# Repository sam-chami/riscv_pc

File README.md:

# riscv_pc

A carrier board for the Lichee RV RISC-V SOM (System On Module).

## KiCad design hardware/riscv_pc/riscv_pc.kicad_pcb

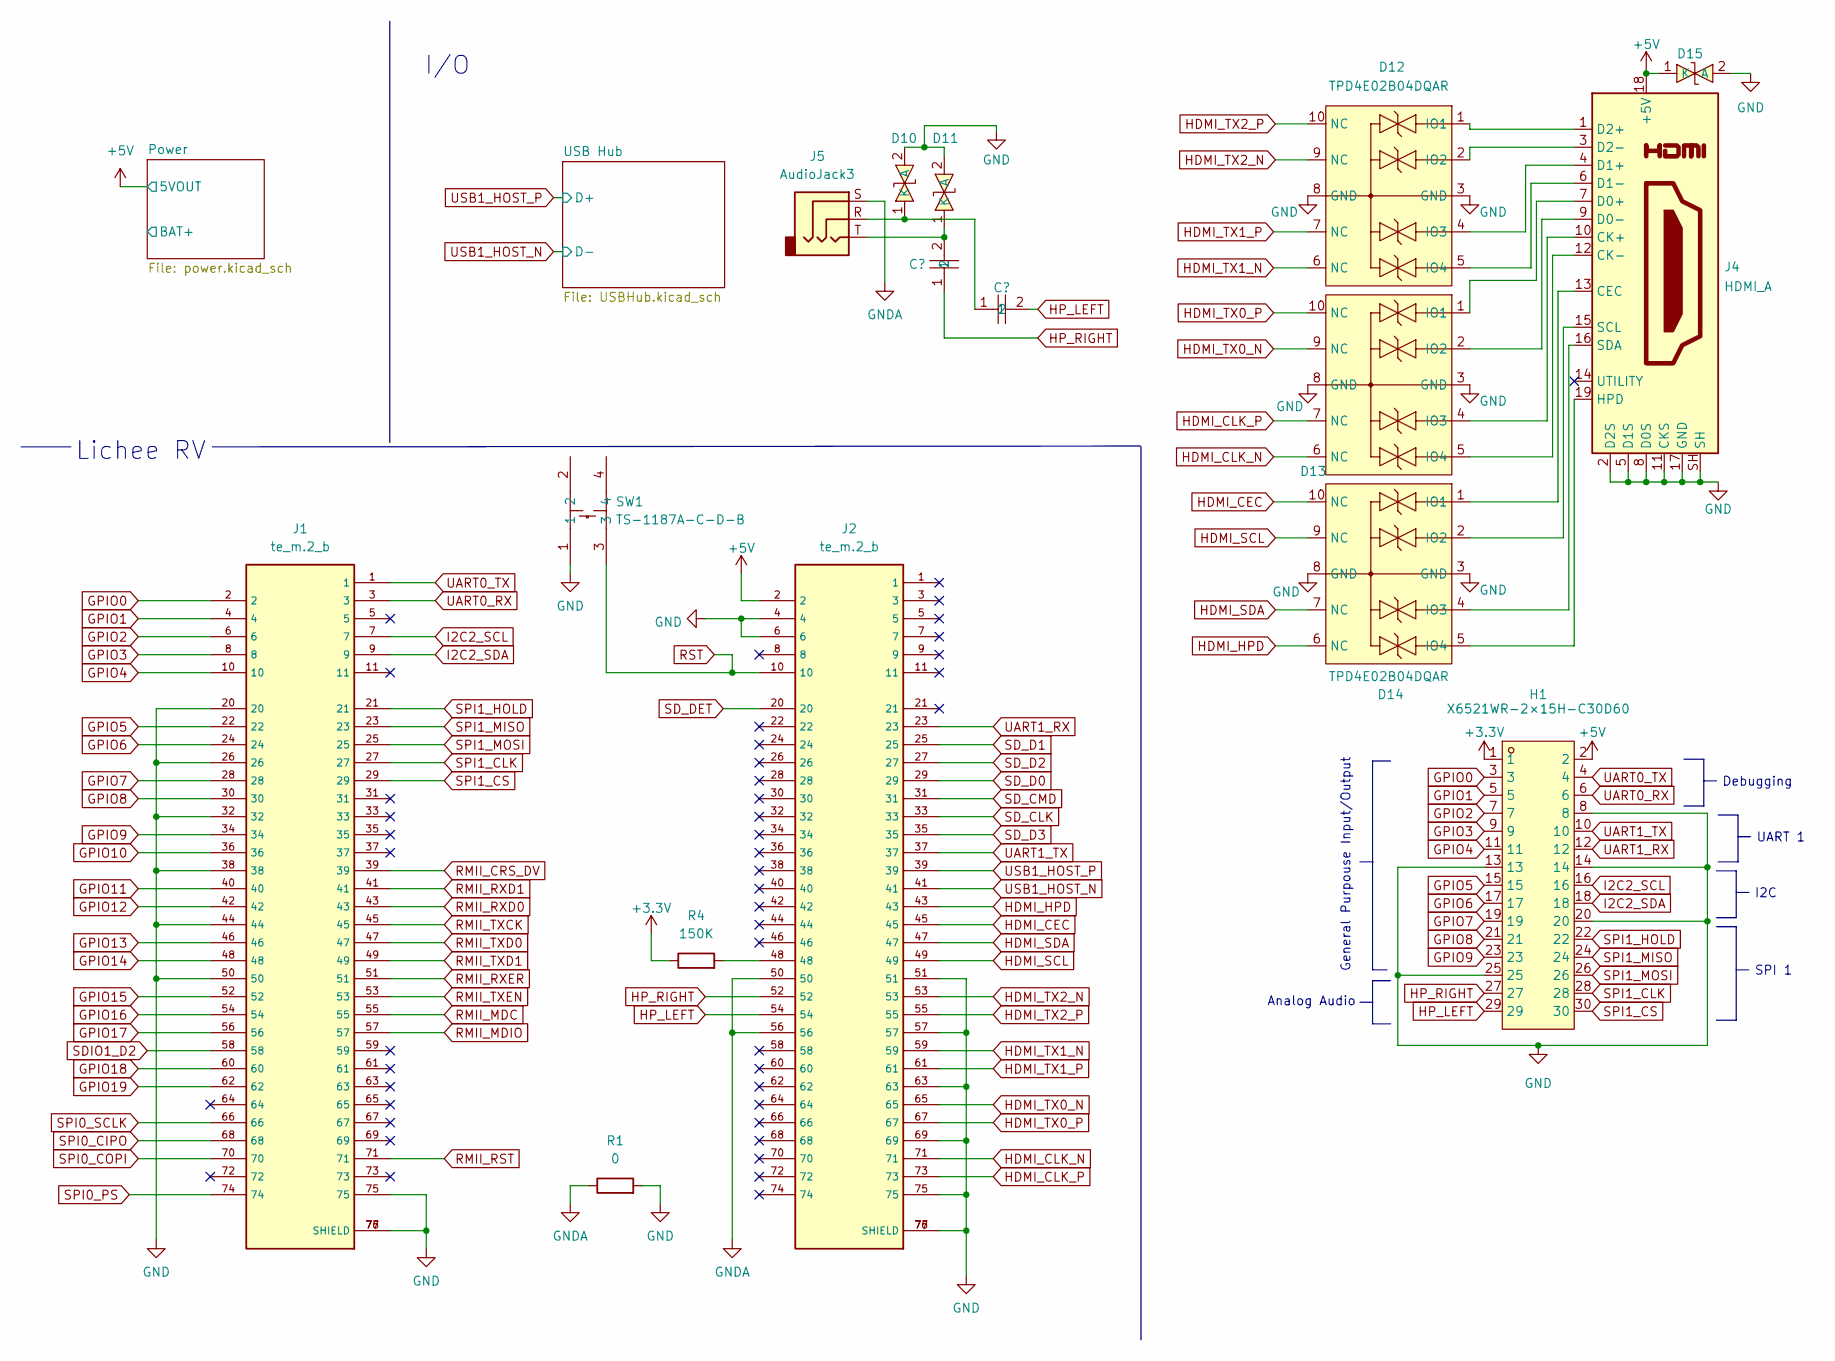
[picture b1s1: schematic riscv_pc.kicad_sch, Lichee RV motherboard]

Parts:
D10, D11, D15: GBLC08C-LF-T7; SOD-323_L1.8-W1.3-LS2.5-BI; LCSC Part C282422
D12, D13, D14: TPD4E02B04DQAR; USON-10_L2.5-W1.0-P0.50-BL; LCSC Part C106794
H1: X6521WR-2×15H-C30D60; HDR-TH_30P-P2.54-H-M-R2-C15-S2.54; LCSC Part C725927
J1, J2: te_m.2_b; CONN-SMD_AS0BC21-S30BB-7H; JLC C2761526
J4: HDMI_A; HDMI-SMD_HDMI-001S; JLC C720616
J5: AudioJack3; AUDIO-TH_PJ313D; JLC C18167
R1: 0; R_0603_1608Metric
R4: 150K; R_0603_1608Metric; JLC C22807
SW1: TS-1187A-C-D-B; KEY-SMD_4P-L5.2-W5.2-P3.7-LS6.4-TL; LCSC Part C318888

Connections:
+5V: D15.1 (K), H1.2, J2.2, J4.18 (+5V); also elsewhere on the board
GND: D10.2 (A), D11.2 (A), D12.3 (GND), D12.8 (GND), D13.3 (GND), D13.8 (GND), D14.3 (GND), D14.8 (GND), D15.2 (A), H1.8, H1.13, H1.14, H1.20, H1.25, J1.20, J1.26, J1.32, J1.38, J1.44, J1.50, J1.75, J1.76 (SHIELD), J1.77 (SHIELD), J2.4, J2.6, J2.51, J2.57, J2.63, J2.69, J2.75, J2.76 (SHIELD), J2.77 (SHIELD), J4.2 (D2S), J4.5 (D1S), J4.8 (D0S), J4.11 (CKS), J4.17 (GND), J4.SH, R1.2, SW1.1; also elsewhere on the board
GNDA: J2.50, J2.56, J5.S, R1.1
GPIO0: H1.3, J1.2
GPIO1: H1.5, J1.4
GPIO2: H1.7, J1.6
GPIO3: H1.9, J1.8
GPIO4: H1.11, J1.10
GPIO5: H1.15, J1.22
GPIO6: H1.17, J1.24
GPIO7: H1.19, J1.28
GPIO8: H1.21, J1.30
GPIO9: H1.23, J1.34
GPIO10: J1.36
GPIO11: J1.40
GPIO12: J1.42
GPIO13: J1.46
GPIO14: J1.48
GPIO15: J1.52
GPIO16: J1.54
GPIO17: J1.56
GPIO18: J1.60
GPIO19: J1.62
HDMI_CEC: D14.10 (NC), J2.45
HDMI_CLK_N: D13.6 (NC), J2.71
HDMI_CLK_P: D13.7 (NC), J2.73
HDMI_HPD: D14.6 (NC), J2.43
HDMI_SCL: D14.9 (NC), J2.49
HDMI_SDA: D14.7 (NC), J2.47
HDMI_TX0_N: D13.9 (NC), J2.65
HDMI_TX0_P: D13.10 (NC), J2.67
HDMI_TX1_N: D12.6 (NC), J2.59
HDMI_TX1_P: D12.7 (NC), J2.61
HDMI_TX2_N: D12.9 (NC), J2.53
HDMI_TX2_P: D12.10 (NC), J2.55
HP_LEFT: H1.29, J2.54; also elsewhere on the board
HP_RIGHT: H1.27, J2.52; also elsewhere on the board
I2C2_SCL: H1.16, J1.7
I2C2_SDA: H1.18, J1.9
unnamed 50: D10.1 (K), J5.R; also elsewhere on the board
unnamed 51: D11.1 (K), J5.T; also elsewhere on the board
unnamed: D12.1 (IO1), J4.1 (D2+)
unnamed: D12.2 (IO2), J4.3 (D2-)
unnamed: D12.4 (IO3), J4.4 (D1+)
unnamed: D12.5 (IO4), J4.6 (D1-)
unnamed: D13.1 (IO1), J4.7 (D0+)
unnamed: D13.2 (IO2), J4.9 (D0-)
unnamed: D13.4 (IO3), J4.10 (CK+)
unnamed: D13.5 (IO4), J4.12 (CK-)
unnamed: D14.1 (IO1), J4.13 (CEC)
unnamed: D14.2 (IO2), J4.15 (SCL)
unnamed: D14.4 (IO3), J4.16 (SDA)
unnamed: D14.5 (IO4), J4.19 (HPD)
unnamed: J2.48, R4.2
RMII_CRS_DV: J1.39
RMII_MDC: J1.55
RMII_MDIO: J1.57
RMII_RST: J1.71
RMII_RXD0: J1.43
RMII_RXD1: J1.41
RMII_RXER: J1.51
RMII_TXCK: J1.45
RMII_TXD0: J1.47
RMII_TXD1: J1.49
RMII_TXEN: J1.53
RST: J2.10, SW1.3
SDIO1_D2: J1.58
SD_CLK: J2.33
SD_CMD: J2.31
SD_D0: J2.29
SD_D1: J2.25
SD_D2: J2.27
SD_D3: J2.35
SD_DET: J2.20
SPI0_CIPO: J1.68
SPI0_COPI: J1.70
SPI0_PS: J1.74
SPI0_SCLK: J1.66
SPI1_CLK: H1.28, J1.27
SPI1_CS: H1.30, J1.29
SPI1_HOLD: H1.22, J1.21
SPI1_MISO: H1.24, J1.23
SPI1_MOSI: H1.26, J1.25
UART0_RX: H1.6, J1.3
UART0_TX: H1.4, J1.1
UART1_RX: H1.12, J2.23
UART1_TX: H1.10, J2.37
USB1_HOST_N: J2.41; also elsewhere on the board
USB1_HOST_P: J2.39; also elsewhere on the board

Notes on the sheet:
UART 1
I2C
Lichee RV
Debugging
I/O
SPI 1
General Purpouse Input/Output
Analog Audio

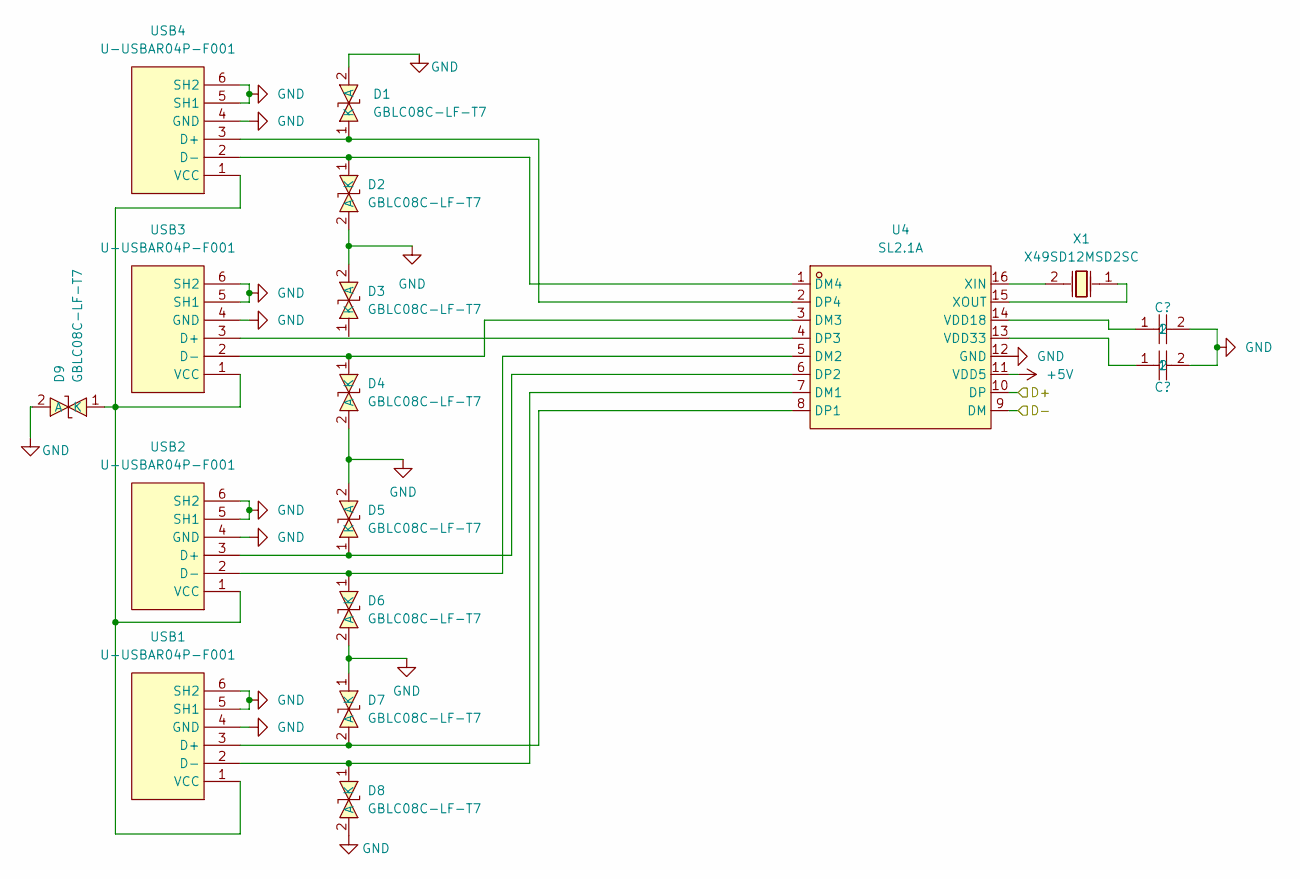
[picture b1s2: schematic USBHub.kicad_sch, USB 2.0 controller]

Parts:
D1, D2, D3, D4, D5, D6, D7, D8, D9: GBLC08C-LF-T7; SOD-323_L1.8-W1.3-LS2.5-BI; LCSC Part C282422
U4: SL2.1A; SOP-16_L10.0-W3.9-P1.27-LS6.0-BL; LCSC Part C192893
USB1, USB2, USB3, USB4: U-USBAR04P-F001; USB-A-TH_USB-302-T; LCSC Part C386736
X1: X49SD12MSD2SC; HC-49US_L11.5-W4.5-P4.88; LCSC Part C16369

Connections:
+5V: U4.11 (VDD5); also elsewhere on the board
GND: D1.2 (A), D2.2 (A), D3.2 (A), D4.2 (A), D5.2 (A), D6.2 (A), D7.1 (K), D8.2 (A), D9.2 (A), U4.12 (GND), USB1.4 (GND), USB1.5 (SH1), USB1.6 (SH2), USB2.4 (GND), USB2.5 (SH1), USB2.6 (SH2), USB3.4 (GND), USB3.5 (SH1), USB3.6 (SH2), USB4.4 (GND), USB4.5 (SH1), USB4.6 (SH2); also elsewhere on the board
unnamed: D1.1 (K), U4.2 (DP4), USB4.3 (D+)
unnamed: D2.1 (K), U4.1 (DM4), USB4.2 (D-)
unnamed: D4.1 (K), U4.3 (DM3), USB3.2 (D-)
unnamed: D5.1 (K), U4.6 (DP2), USB2.3 (D+)
unnamed: D6.1 (K), U4.5 (DM2), USB2.2 (D-)
unnamed: D7.2 (A), U4.8 (DP1), USB1.3 (D+)
unnamed: D8.1 (K), U4.7 (DM1), USB1.2 (D-)
unnamed: D9.1 (K), USB1.1 (VCC), USB2.1 (VCC), USB3.1 (VCC), USB4.1 (VCC)
unnamed: U4.4 (DP3), USB3.3 (D+)
unnamed 68: U4.13 (VDD33); also elsewhere on the board
unnamed 69: U4.14 (VDD18); also elsewhere on the board
unnamed: U4.15 (XOUT), X1.1
unnamed: U4.16 (XIN), X1.2
USB1_HOST_N: U4.9 (DM); also elsewhere on the board
USB1_HOST_P: U4.10 (DP); also elsewhere on the board

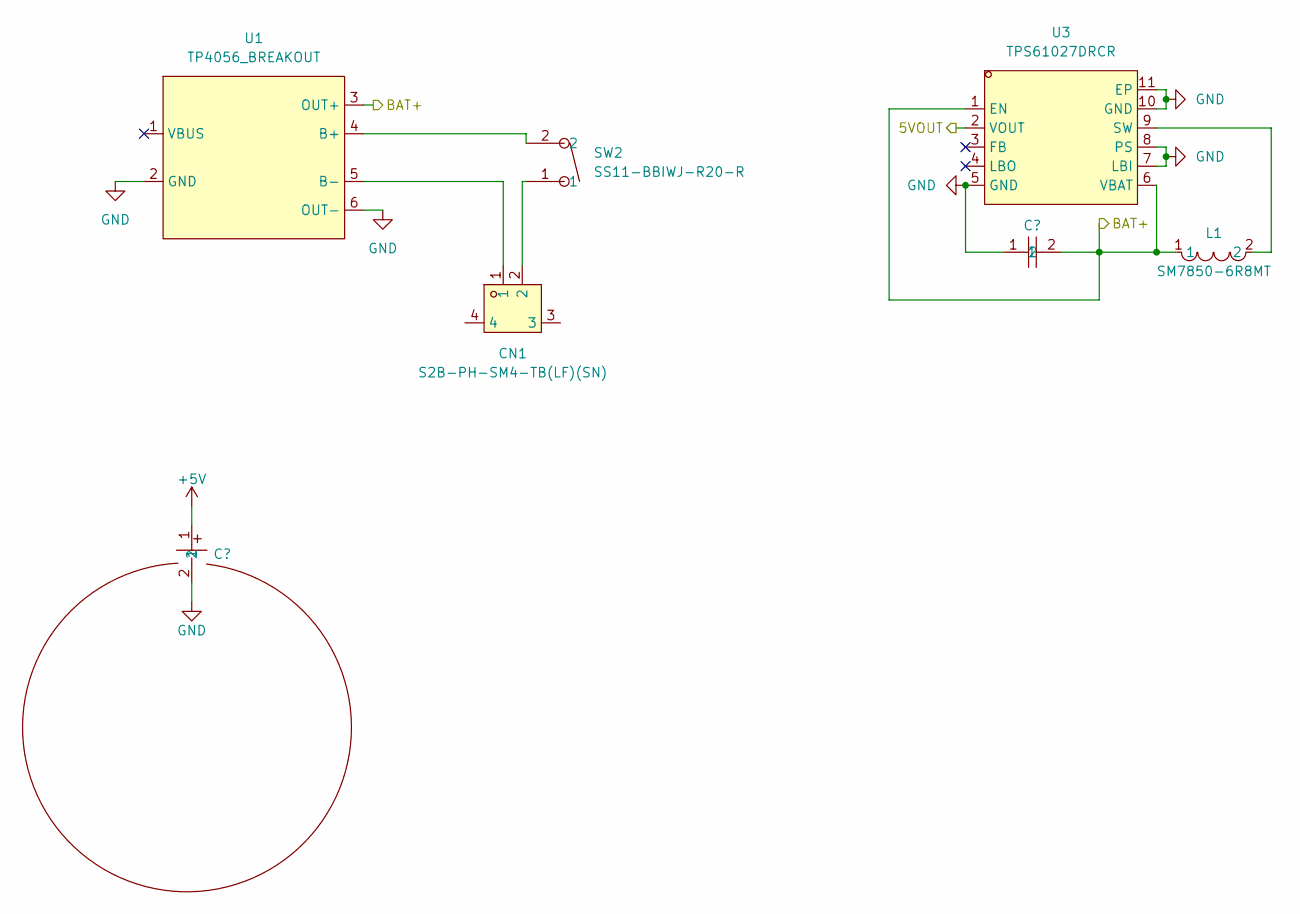
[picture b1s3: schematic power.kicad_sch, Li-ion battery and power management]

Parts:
CN1: S2B-PH-SM4-TB(LF)(SN); CONN-SMD_P2.00_S2B-PH-SM4-TB-LF-SN; LCSC Part C295747
L1: SM7850-6R8MT; IND-SMD_L7.8-W7.0; LCSC Part C10154
SW2: SS11-BBIWJ-R20-R; SW-TH_SS11-BBIWJ-R20-R; LCSC Part C309070
U1: TP4056_BREAKOUT
U3: TPS61027DRCR; VSON-10_L3.0-W3.0-P0.50-TL-EP_TPS62410DRCR; LCSC Part C80258

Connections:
+5V: U3.2 (VOUT); also elsewhere on the board
/Power/BAT+: L1.1, U1.3 (OUT+), U3.1 (EN), U3.6 (VBAT); also elsewhere on the board
GND: U1.2 (GND), U1.6 (OUT-), U3.5 (GND), U3.7 (LBI), U3.8 (PS), U3.10 (GND), U3.11 (EP); also elsewhere on the board
unnamed: CN1.1, U1.5 (B-)
unnamed: CN1.2, SW2.1
unnamed: L1.2, U3.9 (SW)
unnamed: SW2.2, U1.4 (B+)

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
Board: 2 copper layers, 40 parts (0 on the bottom side), 74 nets, no tracks yet.

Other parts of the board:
C1, C2, C4, C5, C6: CL31A106KBHNNNE; C1206
C3: UWX1C101MCL1GB; CAP-SMD_BD6.3-L6.6-W6.6-FD

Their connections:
+5V: C3.1; also elsewhere on the board
/Power/BAT+: C4.2; also elsewhere on the board
GND: C3.2, C4.1, C5.2, C6.2; also elsewhere on the board
HP_LEFT: C2.2; also elsewhere on the board
HP_RIGHT: C1.1; also elsewhere on the board
unnamed 50: C2.1; also elsewhere on the board
unnamed 51: C1.2; also elsewhere on the board
unnamed 68: C6.1; also elsewhere on the board
unnamed 69: C5.1; also elsewhere on the board

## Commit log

2023-03-05 Add ESD protection to USB Lines
2023-03-05 Add ESD protection to AUX port
2023-03-05 Add PDF file
2023-03-11 Add ESD protection to HDMI
2023-03-12 Add GPIO Header (2x15)
2023-03-12 Create PCB
